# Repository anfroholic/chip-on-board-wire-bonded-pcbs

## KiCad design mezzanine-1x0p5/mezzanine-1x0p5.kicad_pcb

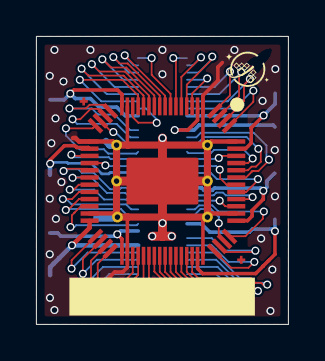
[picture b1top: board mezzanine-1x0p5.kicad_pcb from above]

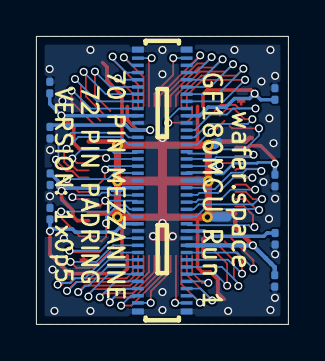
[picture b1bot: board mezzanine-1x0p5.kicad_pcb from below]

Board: 2 copper layers, 14.0 x 16.0 mm, 10 parts (9 on the bottom side), 65 nets.

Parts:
C101, C102, C103, C104, C105, C106, C107, C108: 1uF; C_0201_0603Metric
U101: CONN-SMD_70P-P0.40_HCTL_HC-PBB40C-70DP-0.4V-02
U102: waferspace_1x0p5_padring_v0.1

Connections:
/an_0: U101.21 (in_4), U102.63 (an_0)
/an_1: U101.20 (in_5), U102.64 (an_1)
/an_2: U101.17 (in_6), U102.65 (an_2)
/an_3: U101.16 (in_7), U102.66 (an_3)
/bidir_0: U101.6 (bidir_0), U102.3 (bidir_0)
/bidir_1: U101.5 (bidir_1), U102.4 (bidir_1)
/bidir_2: U101.4 (bidir_2), U102.7 (bidir_2)
/bidir_3: U101.3 (bidir_3), U102.8 (bidir_3)
/bidir_4: U101.2 (bidir_4), U102.9 (bidir_4)
/bidir_5: U101.1 (bidir_5), U102.10 (bidir_5)
/bidir_6: U101.70 (bidir_6), U102.11 (bidir_6)
/bidir_7: U101.69 (bidir_7), U102.12 (bidir_7)
/bidir_8: U101.68 (bidir_8), U102.13 (bidir_8)
/bidir_9: U101.67 (bidir_9), U102.14 (bidir_9)
/bidir_10: U101.66 (bidir_10), U102.15 (bidir_10)
/bidir_11: U101.65 (bidir_11), U102.16 (bidir_11)
/bidir_12: U101.64 (bidir_12), U102.17 (bidir_12)
/bidir_13: U101.63 (bidir_13), U102.18 (bidir_13)
/bidir_14: U101.60 (bidir_14), U102.21 (bidir_14)
/bidir_15: U101.59 (bidir_15), U102.22 (bidir_15)
/bidir_16: U101.58 (bidir_16), U102.23 (bidir_16)
/bidir_17: U101.57 (bidir_17), U102.24 (bidir_17)
/bidir_18: U101.56 (bidir_18), U102.27 (bidir_18)
/bidir_19: U101.55 (bidir_19), U102.28 (bidir_19)
/bidir_20: U101.52 (bidir_20), U102.29 (bidir_20)
/bidir_21: U101.51 (bidir_21), U102.30 (bidir_21)
/bidir_22: U101.50 (bidir_22), U102.31 (bidir_22)
/bidir_23: U101.49 (bidir_23), U102.32 (bidir_23)
/bidir_24: U101.48 (bidir_24), U102.33 (bidir_24)
/bidir_25: U101.47 (bidir_25), U102.34 (bidir_25)
/bidir_26: U101.43 (bidir_26), U102.37 (bidir_26)
/bidir_27: U101.42 (bidir_27), U102.38 (bidir_27)
/bidir_28: U101.41 (bidir_28), U102.39 (bidir_28)
/bidir_29: U101.40 (bidir_29), U102.40 (bidir_29)
/bidir_30: U101.39 (bidir_30), U102.43 (bidir_30)
/bidir_31: U101.38 (bidir_31), U102.44 (bidir_31)
/bidir_32: U101.37 (bidir_32), U102.45 (bidir_32)
/bidir_33: U101.36 (bidir_33), U102.46 (bidir_33)
/bidir_34: U101.35 (bidir_34), U102.47 (bidir_34)
/bidir_35: U101.34 (bidir_35), U102.48 (bidir_35)
/bidir_36: U101.33 (bidir_36), U102.49 (bidir_36)
/bidir_37: U101.32 (bidir_37), U102.50 (bidir_37)
/bidir_38: U101.31 (bidir_38), U102.51 (bidir_38)
/bidir_39: U101.30 (bidir_39), U102.52 (bidir_39)
/bidir_40: U101.29 (an_0), U102.53 (bidir_40)
/bidir_41: U101.28 (an_1), U102.54 (bidir_41)
/bidir_42: U101.27 (in_0), U102.57 (bidir_42)
/bidir_43: U101.26 (in_1), U102.58 (bidir_43)
/bidir_44: U101.23 (in_2), U102.59 (bidir_44)
/bidir_45: U101.22 (in_3), U102.60 (bidir_45)
/clk: U101.8 (clk), U102.1 (clk)
/in_0: U101.12 (in_11), U102.67 (in_0)
/in_1: U101.13 (in_10), U102.68 (in_1)
/in_2: U101.14 (in_9), U102.69 (in_2)
/in_3: U101.15 (in_8), U102.70 (in_3)
/rst_n: U101.7 (rst_n), U102.2 (rst_n)
GND: C101.2, C102.2, C103.2, C104.2, C105.2, C106.2, C107.2, C108.2, U101.10 (GND), U101.18 (GND), U101.25 (GND), U101.45 (GND), U101.53 (GND), U101.61 (GND), U101.MP, U102.5 (GND), U102.19 (GND), U102.25 (GND), U102.35 (GND), U102.42 (GND), U102.56 (GND), U102.62 (GND), U102.72 (GND), U102.75 (MP)
PWR_AUX_0: C105.1, U101.54 (PWR_AUX), U102.26 (VDD)
PWR_AUX_1: C106.1, U101.19 (PWR_AUX), U102.61 (VDD)
VDD_CORE_0: C103.1, U101.46 (VDD_CORE), U102.41 (VDD)
VDD_CORE_1: C104.1, U101.11 (VDD_CORE), U102.6 (VDD)
VDD_IO_0: C107.1, U101.62 (VDD_IO), U102.20 (VDD)
VDD_IO_1: C101.1, U101.44 (VDD_IO), U102.36 (VDD)
VDD_IO_2: C108.1, U101.24 (VDD_IO), U102.55 (VDD)
VDD_IO_3: C102.1, U101.9 (VDD_IO), U102.71 (VDD)

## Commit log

2026-05-09 create 1xp5 panel
2026-05-16 create test p5x1
2026-05-18 more clearance for 1xp5
    PCB house complained about clearance, kicad file was created with exact clearance. I reduced it so we should be good.
2026-05-18 panelize rev1 1xp5
2026-05-23 remove two inner layers on panel
2026-06-16 unsure
